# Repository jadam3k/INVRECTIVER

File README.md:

# INVRECTIVER

## About The Project.

INVRECTIVER is a 12V DC to 230V AC inverter, but of course it does not end there.

After creating dangerous 230V AC, the circuit converts it back down, rectifies it and gives you 24V DC. So basically you get a completely pointless, extremely inefficient and massively overcomplicated 12V to 24V boost converter.

12V DC -> 230V AC -> 24V DC

Does this make any sense? probably not.

Is it cool? yes.

## WARNING

This board generates 230V AC.

It can shock you, destroy components, start a fire or do all of these things at the same time.

Do not touch the high voltage side while the board is powered. Use proper insulation, fuses and common sense. Building or using this project is entirely at your own risk.

## PHOTOS

## BOM

| Nr | Ref                                     | Value             | Footprint                                                | Qty |
| -: | --------------------------------------- | ----------------- | -------------------------------------------------------- | --: |
|  1 | C1                                      | 100nF             | C_0603_1608Metric                                        |   1 |
|  2 | C2                                      | 2200uF            | CP_Radial_D16.0mm_P7.50mm                                |   1 |
|  3 | C3                                      | 0.33uF            | C_0603_1608Metric                                        |   1 |
|  4 | C4                                      | 10uF              | CP_Radial_D5.0mm_P2.00mm                                 |   1 |
|  5 | R1, R4, R5                              | 100K              | R_2010_5025Metric                                        |   3 |
|  6 | R2, R3                                  | 51k               | R_2010_5025Metric                                        |   2 |
|  7 | R6, R7                                  | 470               | R_2010_5025Metric                                        |   2 |
|  8 | R8                                      | 1                 | R_2010_5025Metric                                        |   1 |
|  9 | D1                                      | GBU4M             | Diode_Bridge_Vishay_GBU                                  |   1 |
| 10 | U1                                      | TL494             | DIP-16_W7.62mm                                           |   1 |
| 11 | U2                                      | LM7824_TO220      | TO-220-3_Vertical                                        |   1 |
| 12 | Q1, Q2, Q3, Q4, Q5, Q6, Q7, Q8, Q9, Q10 | IRF3205           | TO-220-3_Vertical                                        |  10 |
| 13 | Q11                                     | TIP2955           | TO-218-3_Vertical                                        |   1 |
| 14 | T1                                      | 12-230            | Transformer_CHK_EI30-2VA_2xSec                           |   1 |
| 15 | T2                                      | Transformer_1P_1S | Transformer_37x44                                        |   1 |
| 16 | J1                                      | 12VDC             | TerminalBlock_Phoenix_MKDS-1,5-2_1x02_P5.00mm_Horizontal |   1 |
| 17 | J2                                      | 24V               | TerminalBlock_Phoenix_MKDS-1,5-2_1x02_P5.00mm_Horizontal |   1 |

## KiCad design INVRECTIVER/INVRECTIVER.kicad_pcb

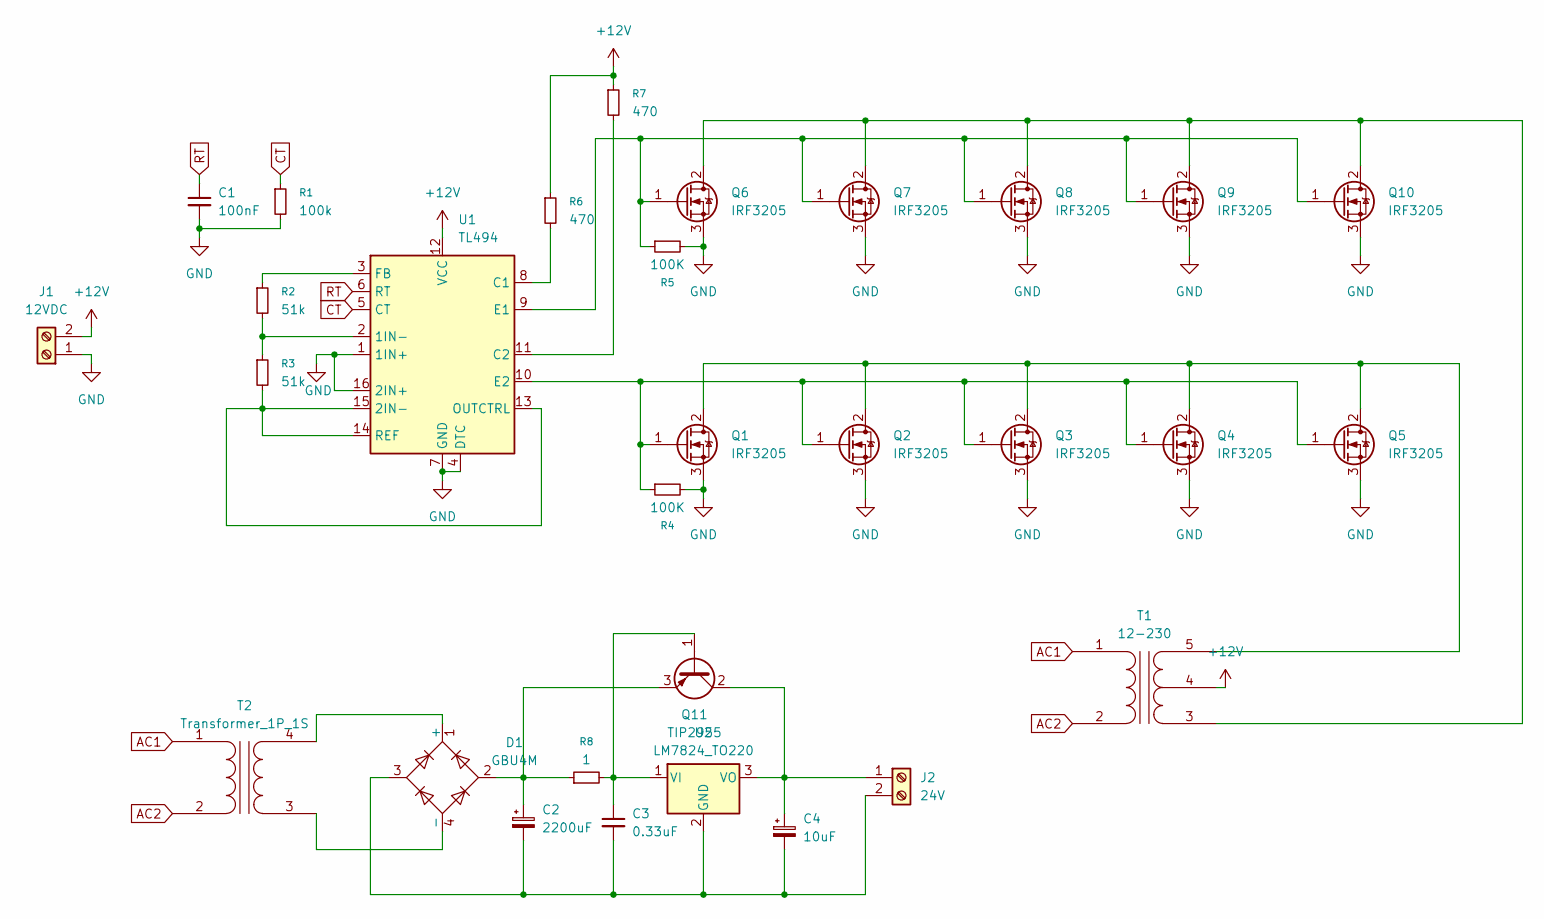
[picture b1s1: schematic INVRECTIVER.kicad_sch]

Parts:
C1: 100nF; C_0603_1608Metric
C2: 2200uF; CP_Radial_D16.0mm_P7.50mm
C3: 0.33uF; C_0603_1608Metric
C4: 10uF; CP_Radial_D5.0mm_P2.00mm
D1: GBU4M; Diode_Bridge_Vishay_GBU
J1: 12VDC; TerminalBlock_Phoenix_MKDS-1,5-2_1x02_P5.00mm_Horizontal
J2: 24V; TerminalBlock_Phoenix_MKDS-1,5-2_1x02_P5.00mm_Horizontal
Q1, Q2, Q3, Q4, Q5, Q6, Q7, Q8, Q9, Q10: IRF3205; TO-220-3_Vertical
Q11: TIP2955; TO-218-3_Vertical
R1: 100k; R_2010_5025Metric
R2, R3: 51k; R_2010_5025Metric
R4, R5: 100K; R_2010_5025Metric
R6, R7: 470; R_2010_5025Metric
R8: 1; R_2010_5025Metric
T1: 12-230; Transformer_CHK_EI30-2VA_2xSec
T2: Transformer_1P_1S; Transformer_37x44
U1: TL494; DIP-16_W7.62mm
U2: LM7824_TO220; TO-220-3_Vertical

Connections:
+12V: J1.2, R6.1, R7.1, T1.4 (SC), U1.12 (VCC)
AC1: T1.1 (AA), T2.1 (AA)
AC2: T1.2 (AB), T2.2 (AB)
CT: R1.1, U1.5 (CT)
GND: C1.2, J1.1, Q1.3 (S), Q2.3 (S), Q3.3 (S), Q4.3 (S), Q5.3 (S), Q6.3 (S), Q7.3 (S), Q8.3 (S), Q9.3 (S), Q10.3 (S), R1.2, R4.2, R5.2, U1.1 (1IN+), U1.4 (DTC), U1.7 (GND), U1.16 (2IN+)
unnamed: D1.1 (+), T2.4 (SB)
unnamed: D1.4 (-), T2.3 (SA)
unnamed: C4.1, J2.1, Q11.2 (C), U2.3 (VO)
unnamed: C2.2, C3.2, C4.2, D1.3, J2.2, U2.2 (GND)
unnamed: Q1.2 (D), Q2.2 (D), Q3.2 (D), Q4.2 (D), Q5.2 (D), T1.5 (SB)
unnamed: Q1.1 (G), Q2.1 (G), Q3.1 (G), Q4.1 (G), Q5.1 (G), R4.1, U1.10 (E2)
unnamed: Q6.2 (D), Q7.2 (D), Q8.2 (D), Q9.2 (D), Q10.2 (D), T1.3 (SA)
unnamed: Q6.1 (G), Q7.1 (G), Q8.1 (G), Q9.1 (G), Q10.1 (G), R5.1, U1.9 (E1)
unnamed: C3.1, Q11.1 (B), R8.2, U2.1 (VI)
unnamed: C2.1, D1.2, Q11.3 (E), R8.1
unnamed: R2.2, R3.1, U1.2 (1IN-)
unnamed: R3.2, U1.13 (OUTCTRL), U1.14 (REF), U1.15 (2IN-)
unnamed: R6.2, U1.8 (C1)
unnamed: R7.2, U1.11 (C2)
unnamed: R2.1, U1.3 (FB)
RT: C1.1, U1.6 (RT)

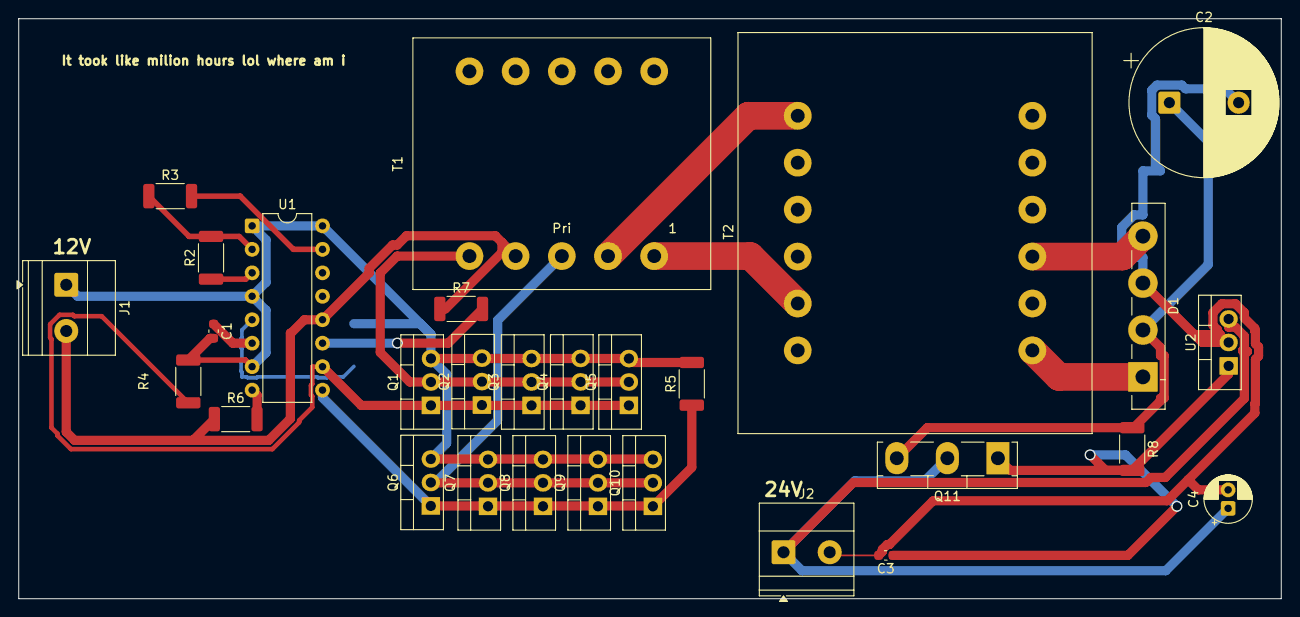
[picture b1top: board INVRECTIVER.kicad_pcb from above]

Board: 2 copper layers, 136.7 x 62.8 mm, 30 parts (1 on the bottom side), 21 nets.

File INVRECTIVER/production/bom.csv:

Designator,Footprint,Quantity,Value,LCSC Part #
C1,0603,1,100nF,
C2,CP_Radial_D16.0mm_P7.50mm,1,2200uF,
C3,0603,1,0.33uF,
C4,CP_Radial_D5.0mm_P2.00mm,1,10uF,
D1,Diode_Bridge_Vishay_GBU,1,GBU4M,
J1,"TerminalBlock_Phoenix_MKDS-1,5-2_1x02_P5.00mm_Horizontal",1,12VDC,
J2,"TerminalBlock_Phoenix_MKDS-1,5-2_1x02_P5.00mm_Horizontal",1,24V,
"Q1, Q10, Q2, Q3, Q4, Q5, Q6, Q7, Q8, Q9",TO-220-3_Vertical,10,IRF3205,
Q11,TO-218-3_Vertical,1,TIP2955,
"R1, R4, R5",2010,3,100k,
"R2, R3",2010,2,51k,
"R6, R7",2010,2,470,
R8,2010,1,1,
T1,Transformer_CHK_EI30-2VA_2xSec,1,12-230,
T2,Transformer_37x44,1,Transformer_1P_1S,
U1,DIP-16_W7.62mm,1,TL494,
U2,TO-220-3_Vertical,1,LM7824_TO220,
